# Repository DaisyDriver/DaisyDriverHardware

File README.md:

# DaisyDriver
The DaisyDriver project aims to make automation a common feature of scientific experiments by providing scientists with a simple, powerful interface to control motors in their setups. The [wiki](https://github.com/fr293/DaisyDriver/wiki/Getting-Started) contains information on how DaisyDrivers are assembled, programmed and operated.

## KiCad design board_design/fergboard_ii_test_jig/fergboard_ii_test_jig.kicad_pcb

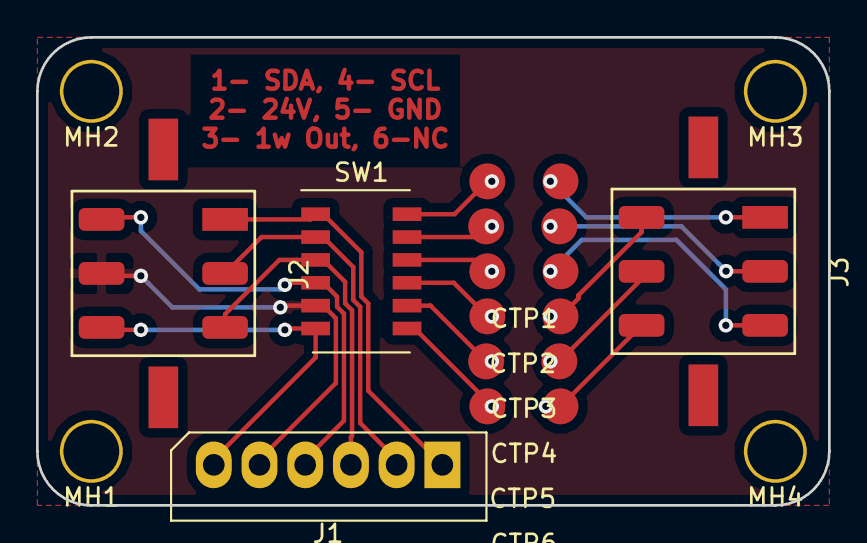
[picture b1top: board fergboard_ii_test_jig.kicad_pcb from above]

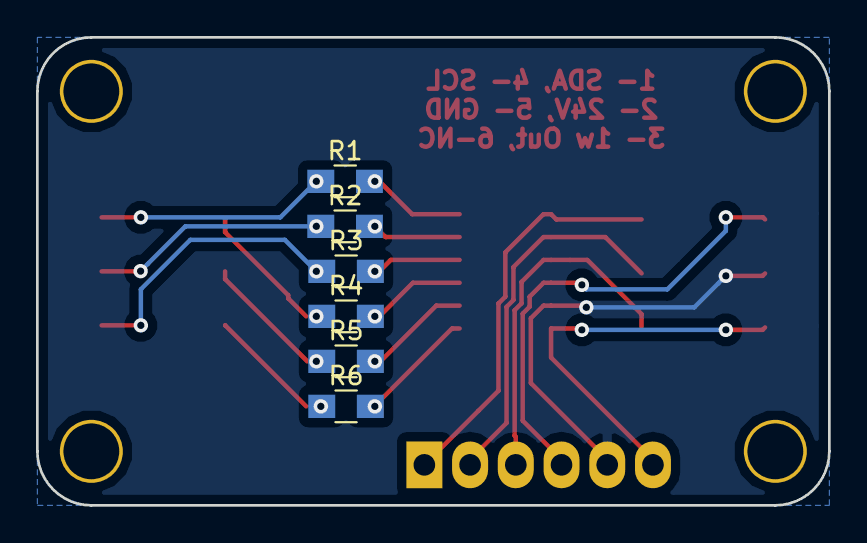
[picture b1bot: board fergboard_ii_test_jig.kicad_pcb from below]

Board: 2 copper layers, 44.0 x 26.0 mm, 20 parts (6 on the bottom side), 18 nets.

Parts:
CTP1, CTP2, CTP3, CTP4, CTP5, CTP6: current_test; Current_test_point
J1: Conn_01x06_Male; Molex_SPOX-5267_22-03-5065_06x2.54mm_Straight
J2, J3: molex_micro_fit_3*2; molex_microfit_3_by_2
MH1, MH2, MH3, MH4: MountingHole_Pad; 3.1_hole
R1, R2, R3, R4, R5, R6: 1R; R_0805_HandSoldering
SW1: SW_DIP_x06; SW_DIP_x6_W5.08mm_Slide_Copal_CHS-A

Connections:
HI_1: CTP1.1, R1.2, SW1.12
HI_2: CTP2.1, R2.2, SW1.11
HI_3: CTP3.1, R3.2, SW1.10
HI_4: CTP4.1, R4.2, SW1.9
HI_5: CTP5.1, R5.2, SW1.8
HI_6: CTP6.1, R6.2, SW1.7
IN_1: J1.1, J2.1, SW1.1
IN_2: J1.2, J2.2, SW1.2
IN_3: J1.3, J2.3, SW1.3
IN_4: J1.4, J2.4, SW1.4
IN_5: J1.5, J2.5, SW1.5
IN_6: J1.6, J2.6, SW1.6
OUT_1: CTP1.2, J3.1, R1.1
OUT_2: CTP2.2, J3.2, R2.1
OUT_3: CTP3.2, J3.3, R3.1
OUT_4: CTP4.2, J3.4, R4.1
OUT_5: CTP5.2, J3.5, R5.1
OUT_6: CTP6.2, J3.6, R6.1

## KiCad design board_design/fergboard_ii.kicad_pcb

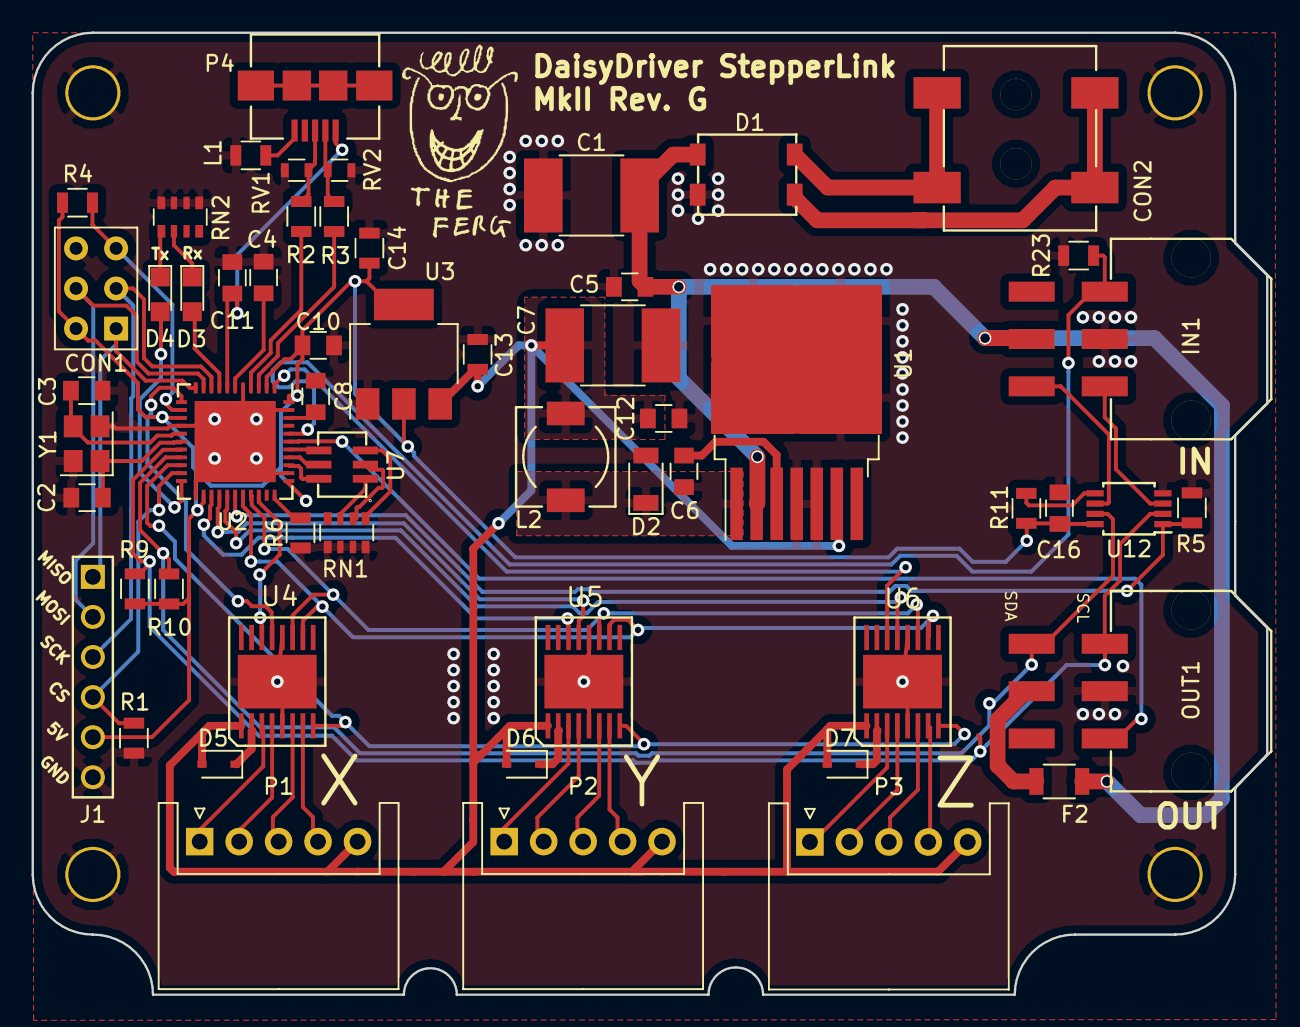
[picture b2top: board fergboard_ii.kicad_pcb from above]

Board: 2 copper layers, 78.2 x 61.0 mm, 61 parts (0 on the bottom side), 67 nets.

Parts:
C1: 33u; R_2816
C2, C3: 18p; C_0805
C4, C12: 1u; C_0805
C5, C8, C10, C11, C16: 100n; C_0805
C6: 10n; C_0805
C7: 330u; R_2816
C13, C14: 10u; R_0805
CON1: AVR-ISP-6; SW_NKK_G1xJP
CON2: BARREL_JACK; SMD_Jack
D1: D_Bridge_+-AA; CD-HD2004
D2: D_Schottky_0V7; D_1206
D3, D4: Yellow; LED_0805
D5, D6, D7: D_Zener; D_SOD-323
F2: 2A_Polyfuse; R_1206
IN1: Molex_micro_fit_3*2; molex_micro_fit_3_by_2_right_angle
J1: Conn_01x06; 1by6_connector
L1: Ferrite_Bead; R_0805
L2: 33u; Choke_SMD_6.3x6.3_H3
OUT1: Molex_micro_fit_3*2; molex_micro_fit_3_by_2_right_angle
P1, P2, P3: CONN_01X05; JST_XH_S05B-XH-A_05x2.50mm_Angled
P4: USB_OTG; USB_Micro_B
R1, R4, R5, R6, R9, R10, R11, R23: 10k; R_0805
R2, R3: 22; R_0805
RN1, RN2: 4k7; R_Array_Convex_4x0603
RV1, RV2: Varistor_[CG0603MLC-05E_Bourns]; R_0603
U1: lm2676_TO-263; TO-263-7_TabPin8
U2: ATMEGA16U4-M-pad-connected; QFN-44-1EP_7x7mm_Pitch0.5mm
U3: lm1117; SOT-223
U4, U5, U6: DRV8805
U7: RGB_LED
U8, U9, U10, U11: hole; 3.1_hole
U12: PCA9511A; TSSOP-8_3x3mm_Pitch0.65mm
U13: ferg_logo; LOGO
Y1: 16M_crystal; Crystal_SMD_3225-4pin_3.2x2.5mm

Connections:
1W_in: IN1.1, R23.2, U2.40
1W_out: OUT1.3, U2.39
BLUE: U2.36, U7.6
CATCH_DIODE: C6.1, D2.1, L2.1, U1.1
CONNECT_INPUTS: R5.2, U2.28, U12.1
CS: J1.4, R1.2, U2.21
D+: P4.3, R2.1, RV1.1
D-: P4.2, R3.1, RV2.1
DIRX: U2.12, U4.13
DIRY: U2.26, U5.13
DIRZ: U2.27, U6.13
ENABLE_MOTORS: U2.20, U4.8, U5.8, U6.8
GREEN: U2.37, U7.5
MCU_POWER: C10.1, C14.1, C16.2, CON1.6, J1.5, R4.2, R9.2, R10.2, R11.1, U2.2, U2.14, U2.24, U2.34, U2.44, U3.2, U3.4, U12.8
MID_POWER_12V: C7.1, C12.1, C13.2, D5.2, D6.2, D7.2, L2.2, P1.5, P2.5, P3.5, U1.6, U3.3, U4.1, U5.1, U6.1
MISO: CON1.1, J1.1, U2.11
MOSI: CON1.5, J1.2, U2.10
unnamed: C2.1, U2.17, Y1.1
unnamed: C3.1, U2.16, Y1.3
unnamed: C4.1, U2.6
unnamed: C6.2, U1.3
unnamed: C8.1, U2.42
unnamed: CON2.1, D1.3
unnamed: CON2.2, CON2.3, D1.4
unnamed: D3.1, RN2.2
unnamed: D4.1, RN2.1
unnamed: D5.1, U4.2
unnamed: D6.1, U5.2
unnamed: D7.1, U6.2
unnamed: F2.1, OUT1.5
unnamed: L1.1, P4.5
unnamed: P1.1, U4.3
unnamed: P1.2, U4.4
unnamed: P1.3, U4.6
unnamed: P1.4, U4.7
unnamed: P2.1, U5.3
unnamed: P2.2, U5.4
unnamed: P2.3, U5.6
unnamed: P2.4, U5.7
unnamed: P3.1, U6.3
unnamed: P3.2, U6.4
unnamed: P3.3, U6.6
unnamed: P3.4, U6.7
unnamed: R2.2, U2.4
unnamed: R3.2, U2.3
unnamed: R6.2, U2.33
unnamed: R11.2, U12.5
unnamed: RN1.1, U7.3
unnamed: RN1.2, U7.2
unnamed: RN1.3, U7.1
POWER_IN_24V: C1.1, C5.1, D1.1, F2.2, IN1.5, U1.2
RED: U2.38, U7.4
RST: CON1.3, R4.1, U2.13
RXLED: D3.2, U2.8
SCK: CON1.2, J1.3, U2.9
SCL: OUT1.1, R9.1, U2.18, U12.2
SCL_IN: IN1.3, U12.3
SDA: OUT1.4, R10.1, U2.19, U12.7
SDA_IN: IN1.6, U12.6
SM0: U2.30, U4.11, U5.11, U6.11
SM1: U2.29, U4.10, U5.10, U6.10
STEPX: U2.31, U4.14
STEPY: U2.25, U5.14
STEPZ: U2.1, U6.14
TXLED: D4.2, U2.22
VBUS: C11.1, P4.1, U2.7
xtalcase: C1.2, C2.2, C3.2, C4.2, C5.2, C7.2, C8.2, C10.2, C11.2, C12.2, C13.1, C14.2, C16.1, CON1.4, D1.2, D2.2, IN1.2, J1.6, L1.2, OUT1.2, R1.1, R5.1, R6.1, R23.1, RN1.5, RN1.6, RN1.7, RN1.8, RN2.5, RN2.6, RN2.7, RN2.8, RV1.2, RV2.2, U1.4, U1.5, U1.8, U2.5, U2.15, U2.23, U2.35, U2.43, U2.45, U3.1, U4.5, U4.12, U5.5, U5.12, U6.5, U6.12, U8.1, U9.1, U10.1, U11.1, U12.4, Y1.2, Y1.4
